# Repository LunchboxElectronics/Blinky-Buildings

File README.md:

# Blinky-Buildings
Blinky Buildings v1
- About:  
Blinky Buildings is a simple kit to teach people how to make derivatives of open source hardware. You are welcome to create a derivative of this kit as long as it abides by the open source hardware definition. 

This kit blinks 20 LEDs from an ATtiny85. The code was written in Arduino and uses a technique called Charlieplexing to drive multiple LEDs using just 5 pins of the ATtiny.

This kit assumes you know how to solder. If not, there are plenty of online tutorials on how to solder. The kit is fairly quick to put together, roughly 10 minutes, and the chip has been programmed for you! 

- Materials and tools:
Here are the parts you’ll need to get stared:
20 LEDs (with a max current of 20mA)
5 Resistors (for 3.2v forward voltage LEDs, I used 680 Ohm resistors)
1 ATtiny85
1 battery holder
1 3v battery
1 switch

Here are the tools you’ll need to get stared:
Soldering Iron
Solder
wire clippers

More information and documentation, including an assembly guide, lives here: bit.ly/blinkybuildings

- Attribution: 
The code for this project was downloaded from http://code.google.com/p/avr-hardware-random-number-generation/ Original code by Geoff  Steele, altered by commenting some code out to blink LEDs on and off by Alicia Gibb.
The original Fritzing design of charlieplexing 20 LEDs was downloaded from http://fritzing.org/projects/charlieplex-snowfallshooting-star-20-leds by Davy Uittenbogerd. Alicia Gibb drew this schematic in Eagle and altered in into the Empire State Blinky Building form factor.
The original code and the hardware files are both under a CC-BY-SA creative commons license.
Code: CC-BY-SA: Geoff Steele
Fritzing layout: CC-BY-SA: Davy Uittenbogerd
Blinky Building schematic, board file and BOM: CC-BY-SA: Alicia Gibb

- Licensing: 
Blinky Buildings is an open source hardware product and follows the open source hardware definition: www.oshwa.org/definition
The license on the source files for Blinky Buildings is CC-BY-SA

Distributed as-is; no warranty given. Not suitable for people who might eat electronics.

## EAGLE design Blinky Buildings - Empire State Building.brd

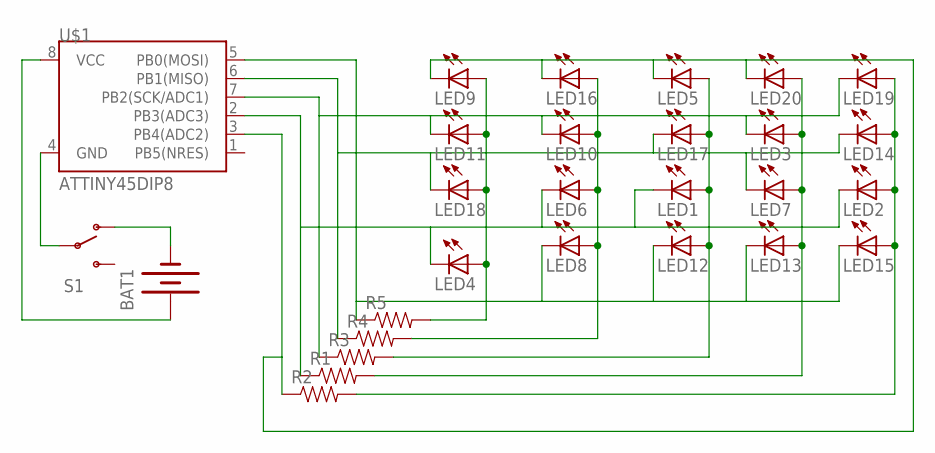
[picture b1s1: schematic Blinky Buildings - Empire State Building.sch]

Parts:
BAT1: BATTERY20PTH; BATTCOM_20MM_PTH
LED1, LED2, LED3, LED4, LED5, LED6, LED7, LED8, LED9, LED10, LED11, LED12, LED13, LED14, LED15, LED16, LED17, LED18, LED19, LED20: LED3MM
R1, R2, R3, R4, R5: RESISTORAXIAL-0.3; AXIAL-0.3
S1: SWITCH-SPSTKIT; SWITCH-SPDT_KIT
U$1: ATTINY45DIP8; DIP08

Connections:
unnamed: LED5.K (C), LED9.K (C), LED16.K (C), LED20.K (C), R2.P$1 (1), U$1.3 (PB4(ADC2))
unnamed: LED1.K (C), LED2.K (C), LED4.K (C), LED6.K (C), R1.P$1 (1), U$1.2 (PB3(ADC3))
unnamed: LED3.K (C), LED10.K (C), LED11.K (C), LED19.K (C), R3.P$1 (1), U$1.7 (PB2(SCK/ADC1))
unnamed: LED7.K (C), LED14.K (C), LED17.K (C), LED18.K (C), R4.P$1 (1), U$1.6 (PB1(MISO))
unnamed: LED8.K (C), LED12.K (C), LED13.K (C), LED15.K (C), R5.P$1 (1), U$1.5 (PB0(MOSI))
unnamed: LED3.A, LED7.A, LED13.A, LED20.A, R1.P$2 (2)
unnamed: LED4.A, LED9.A, LED11.A, LED18.A, R5.P$2 (2)
unnamed: LED6.A, LED8.A, LED10.A, LED16.A, R4.P$2 (2)
unnamed: LED1.A, LED5.A, LED12.A, LED17.A, R3.P$2 (2)
unnamed: LED2.A, LED14.A, LED15.A, LED19.A, R2.P$2 (2)
unnamed: S1.2, U$1.4 (GND)
unnamed: BAT1.1 (+), U$1.8 (VCC)
unnamed: BAT1.2 (-), S1.1 (O)

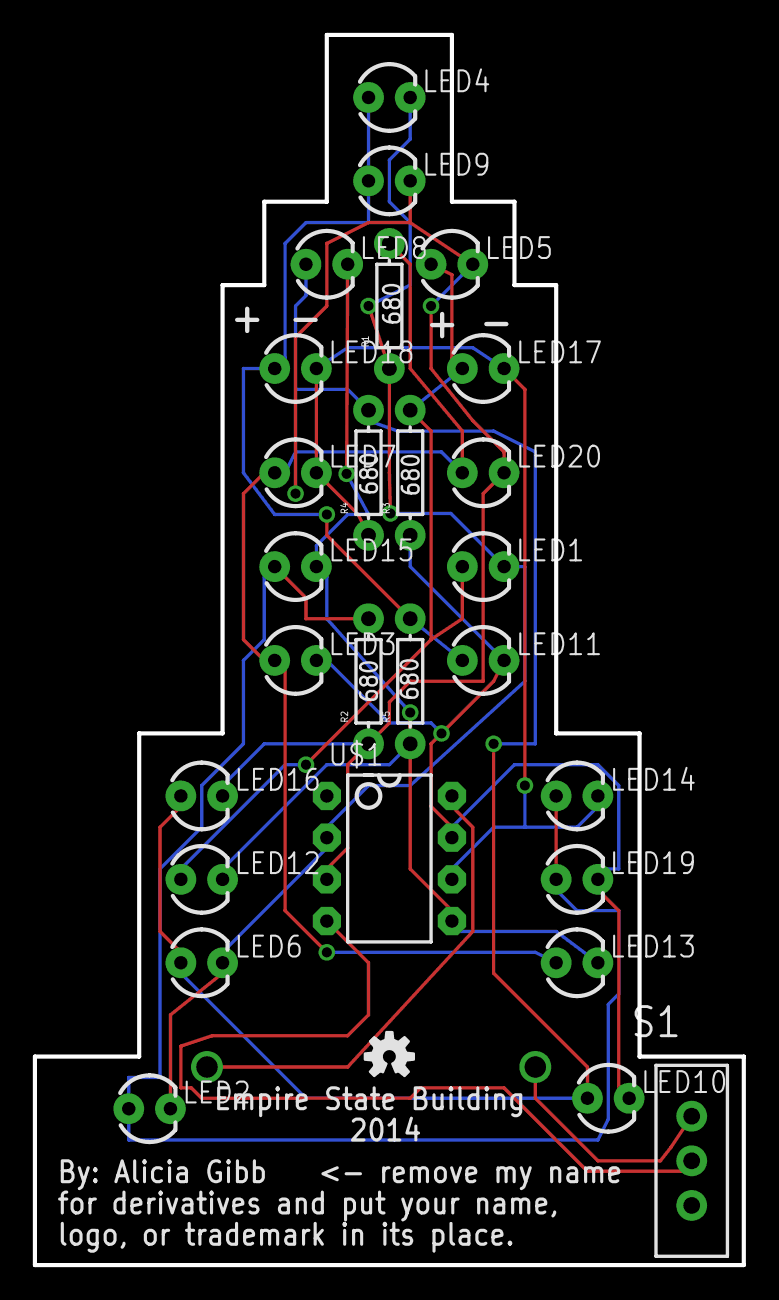
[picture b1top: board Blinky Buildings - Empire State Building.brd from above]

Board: 2 copper layers, 43.2 x 74.9 mm, 29 parts (1 on the bottom side), 13 nets.

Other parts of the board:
U$2: OSHW-LOGO-S

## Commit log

2016-04-27 Added source files via upload

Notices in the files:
parts and their libraries:
SparkFun: Licensing: CC v3.0 Share-Alike You are welcome to use this library for commercial purposes.
